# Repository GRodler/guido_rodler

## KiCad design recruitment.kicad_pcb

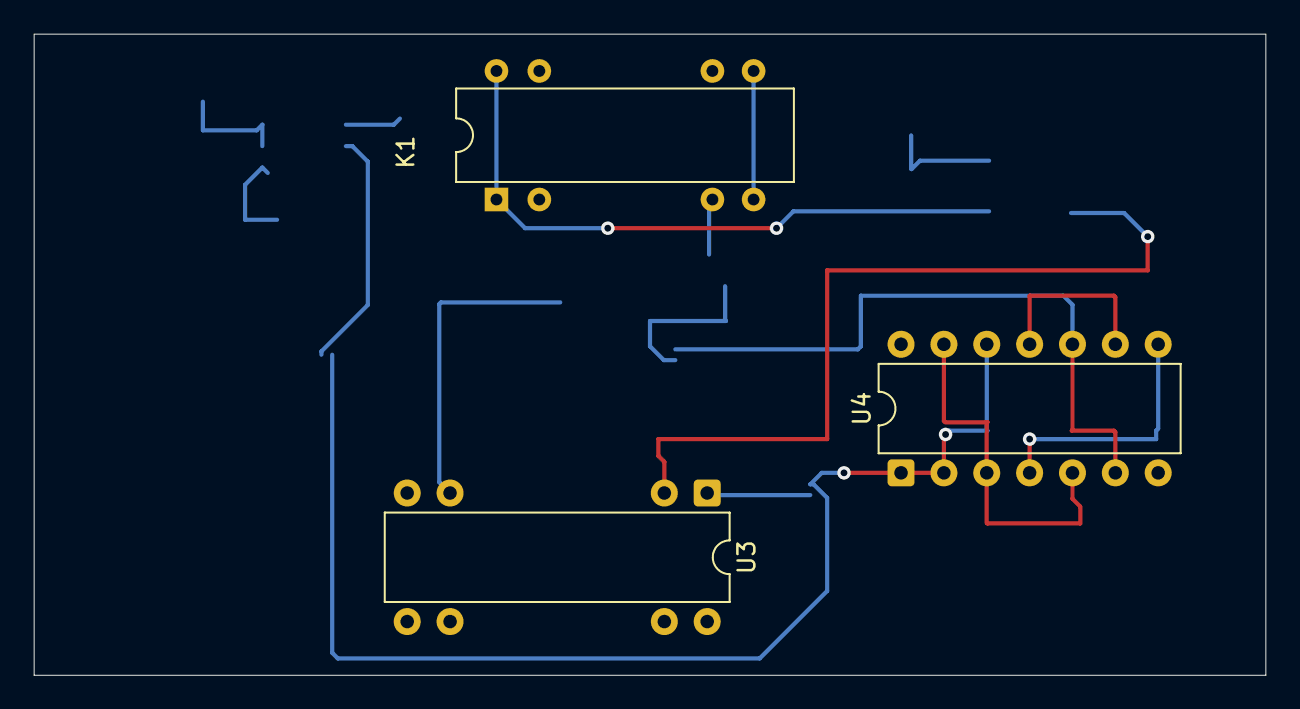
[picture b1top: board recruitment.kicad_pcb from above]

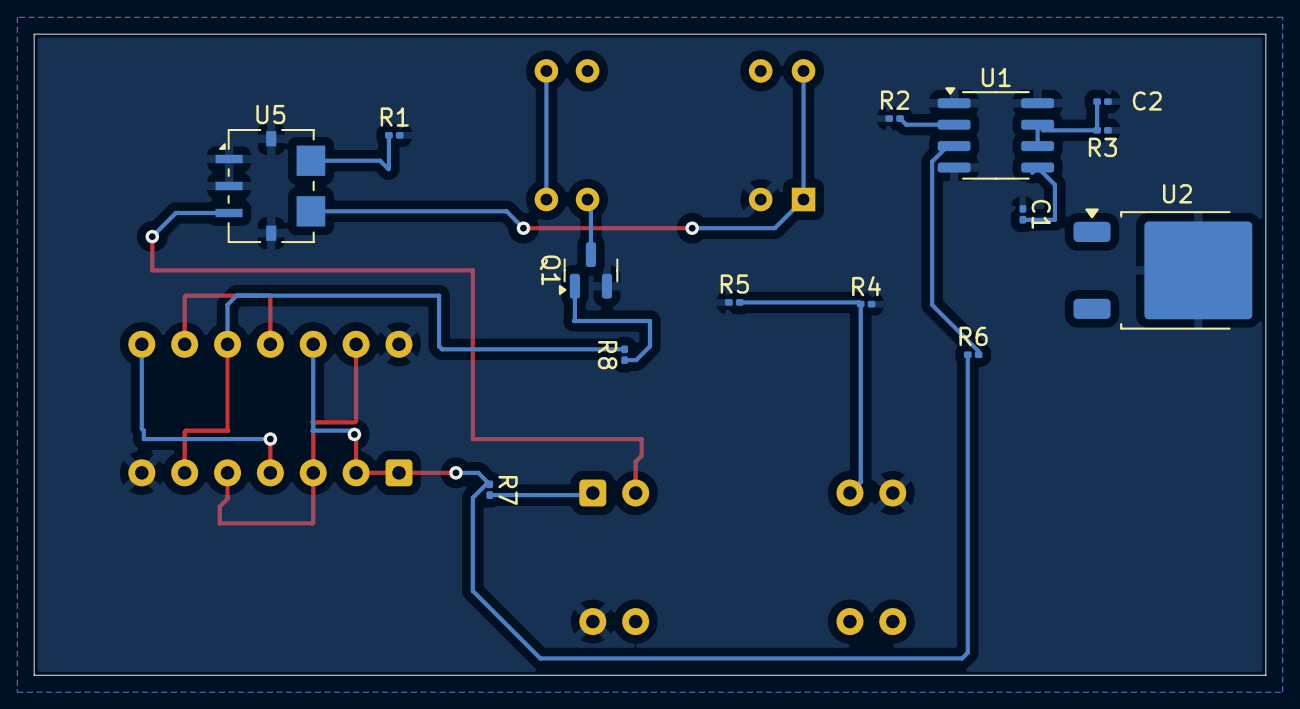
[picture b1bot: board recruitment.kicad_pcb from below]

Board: 2 copper layers, 73.0 x 38.0 mm, 17 parts (14 on the bottom side), 18 nets.

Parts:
C1: 10nF; C_0201_0603Metric
C2: 10uF; C_0201_0603Metric
K1: DIPxx-1Axx-11x; Relay_StandexMeder_DIP_LowProfile
Q1: 2N7002; SOT-23
R1: 3,5; R_0201_0603Metric
R2, R6, R7, R8: 10k; R_0201_0603Metric
R3, R5: 1; R_0201_0603Metric
R4: 1,94; R_0201_0603Metric
U1: NE555D; SOIC-8_3.9x4.9mm_P1.27mm
U2: L7805; TO-252-2
U3: LM393; DIP-8-16_W7.62mm
U4: 7400; DIP-14_W7.62mm
U5: ACS780xLRTR-050U; Allegro_PSOF-7_4.8x6.4mm_P1.60mm

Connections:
/load_system/LOAD_SUPPLY_IN: R1.1, U5.6 (IP-)
/monitor_system/LOAD_SUPPLY_IN: K1.7, K1.8
GND: C1.1, C2.2, K1.2, Q1.2 (S), R1.2, R2.1, R3.1, R4.2, R5.1, U1.1 (GND), U1.4 (R), U1.8 (VCC), U2.2 (GND), U3.4 (V-), U3.8 (V+), U4.7 (GND), U4.14 (VCC), U5.1 (VCC), U5.2 (GND), U5.4 (NC), U5.7 (NC)
unnamed: Q1.1 (G), R8.1
unnamed: R6.1, R7.1, U4.1, U4.2, U4.12
unnamed: R7.2, U3.1
unnamed: R8.2, U4.6, U4.10
unnamed: C1.2, U1.5 (CV)
unnamed: C2.1, R3.2, U1.6 (THR), U1.7 (DIS)
unnamed: R2.2, U1.2 (TR)
unnamed: U4.4, U4.8
unnamed: U4.9, U4.11
unnamed: U4.3, U4.5, U4.13
unnamed: K1.1, K1.14, U5.5 (IP+)
Vcoil: K1.6, Q1.3 (D)
Vcompare: R4.1, R5.2, U3.3 (+)
Vout: U3.2 (-), U5.3 (VOUT)
VtimerOut: R6.2, U1.3 (Q)

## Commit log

2025-10-04 feat:added hierarchical sheets and hierarchical labels for input and output
2025-10-04 feat:added first comment and box
2025-10-04 feat:added relay to the monitor system
2025-10-04 feat: added hall sensor to the monitor system
2025-10-07 fix:fixed hall sensor connections
2025-10-07 feat:added resistor as a load and added demo connections to minimize ERC errors(2)
2025-10-07 feat:added default kicad .gitignore from:https://github.com/github/gitignore/blob/master/KiCad.gitignore
2025-10-10 feat:added folder for singular components simulations
    feat:added first component simulation: current stabilizer
    fix:changed connection in the monitor system for better visualization
2025-10-11 fix:fixed connection in hall sensor LtSpice simulation
    fix:fixed wrong datasheet assigned to Hall sensor symbol in kicad
2025-10-12 feat: new Circuit elements in the schematic and new LTspice Model
    feat:added latch in kicad schematic with relative sheet
    feat:added Analog-comparator in kicad schematic
    feat:added LTspice Analog-comparator model
    feat:added spice model into Models folder for the Analog_comparator
    refactor:moved all LTspice simulation in a single folder for each one
2025-10-13 feat + fix + refactor on the kicad schematic and simulation folder
    feat:added transistor for coil supply
    refractor: deleted latch sheet
    feat: added latch connection
    refractor: the monito logic and the supply are now separated
    feat:added labels for connection
    feat:added falstad NAND latch simulation
2025-10-13 feat on the kicad schematic and the simulation folder
    feat:added voltage Divider
    feat:added ED555 ltSpice simulation
    feat:added ED555 power cycle timer connection in kicad schematic
    ERC:errors(1) warnings(3)
    DRC:not tested
2025-10-14 feat and fix on kicad schematic and pcb
    feat:added resistor capacitor and latch footprints
    feat:added elements in pcb design
    fix: added pull resistors on analog comparator and NAND latch
    ERC: passed warnings(3)
    DRC: not tested
2025-10-14 feat + fix on kicad pcb
    feat:added mass layer
    refactor: moved components for better connection
    fix:added missing footprints to resistors etc.
    ERC: passed warnings(3)
    DRC: errors(42) ;(
2025-10-16 feat + fix + refactor on kicad pcb
    feat:added components connections
    fix: fixed DRC clearence errors
    refactor:moved components in a different layout
    ERC: passed warnings(3)
    DRC: passed no warnings
2025-10-16 feat on project folder
    feat:added ouotput folders with gerber files
    feat:added docs folder with pdf file and csv count of material
